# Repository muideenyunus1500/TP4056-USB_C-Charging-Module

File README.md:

TP4056 USB-C Charging Module
A compact USB-C Li-ion battery charging and protection module designed in **KiCad 9**.
 Overview
This project implements a TP4056-based charging circuit for a single-cell Li-ion battery with battery protection using the DW01A protection IC and FS8205A dual MOSFET.

Features
- USB Type-C input
- TP4056 Li-ion charging IC
- DW01A battery protection
- FS8205A dual MOSFET protection
- Charging status LEDs
- Compact 2-layer PCB
- Designed in KiCad 9

 Repository Contents
- KiCad project files
- Schematic
- PCB layout
- Gerber files
- Drill files
- Bill of Materials (BOM)
- Project images

Image/3d_with_components.png

Image/pcb.png

Image/Schematic.png
 
 Author
**Muideen Olamide**

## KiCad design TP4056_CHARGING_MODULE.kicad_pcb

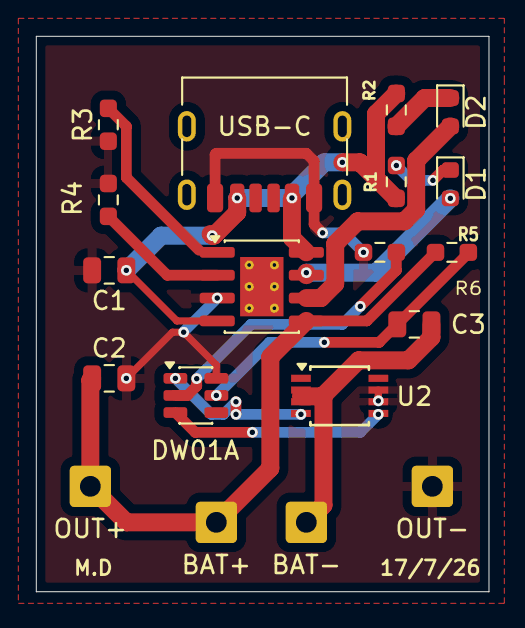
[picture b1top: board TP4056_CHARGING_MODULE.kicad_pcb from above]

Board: 4 copper layers, 25.1 x 30.9 mm, 19 parts (0 on the bottom side), 14 nets.

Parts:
C1, C3: 0.1uf; C_0805_2012Metric
C2: 10uf; C_0805_2012Metric
D1, D2: LED; LED_0603_1608Metric
J2: OUT+; SolderWire-0.5sqmm_1x01_D0.9mm_OD2.3mm
J3: BAT+; SolderWire-0.5sqmm_1x01_D0.9mm_OD2.3mm
J4: BAT-; SolderWire-0.5sqmm_1x01_D0.9mm_OD2.3mm
J5: OUT-; SolderWire-0.5sqmm_1x01_D0.9mm_OD2.3mm
R1, R2, R3, R4: 1k; R_0603_1608Metric_Pad0.98x0.95mm_HandSolder
R5: 1.2k; R_0603_1608Metric_Pad0.98x0.95mm_HandSolder
R6: 100k; R_0603_1608Metric_Pad0.98x0.95mm_HandSolder
U1: TP4056-42-ESOP8; SOIC-8-1EP_3.9x4.9mm_P1.27mm_EP2.41x3.3mm_ThermalVias
U2: DW01A; SOT-23-6
U2#2: TSSOP-8_3x3mm_P0.65mm
USB-C: USB_C; USB_C_Receptacle_HRO_TYPE-C-31-M-17

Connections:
B+: C2.1, J2.1, J3.1, R6.1, U1.5 (BAT)
GND: C1.2, C2.2, J5.1, R3.1, R4.1, R5.1, U1.3 (GND), U2.6 (GND), U2#2.6 (S2), U2#2.7 (S2), USB-C.A12 (GND), USB-C.B12 (GND)
unnamed: D1.2 (A), U1.7 (~CHRG)
unnamed: D1.1 (K), R1.2
unnamed: D2.2 (A), U1.6 (~STDBY)
unnamed: D2.1 (K), R2.2
unnamed: U2.1 (OD), U2#2.4 (G1)
unnamed: U2.3 (OC), U2#2.5 (G2)
unnamed: C3.2, J4.1, U2#2.2 (S1), U2#2.3 (S1)
unnamed: C1.1, R1.1, R2.1, U1.4 (V_{CC}), U1.8 (CE), USB-C.A9 (VBUS), USB-C.B9 (VBUS)
unnamed: R4.2, U1.2 (PROG)
unnamed: R3.2, U1.1 (TEMP)
unnamed: R5.2, U2.2 (CS)
unnamed: C3.1, R6.2, U2.5 (VCC)
